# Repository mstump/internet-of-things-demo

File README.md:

internet-of-things-demo
=======================

Demo of internet of things

## Example Output:
```
motion: 0 | temp: 070.81°F | relative humidity: 045.75 | dew point: 048.85°F | pressure: 029.85 inHg | altitude: 039.20m
```

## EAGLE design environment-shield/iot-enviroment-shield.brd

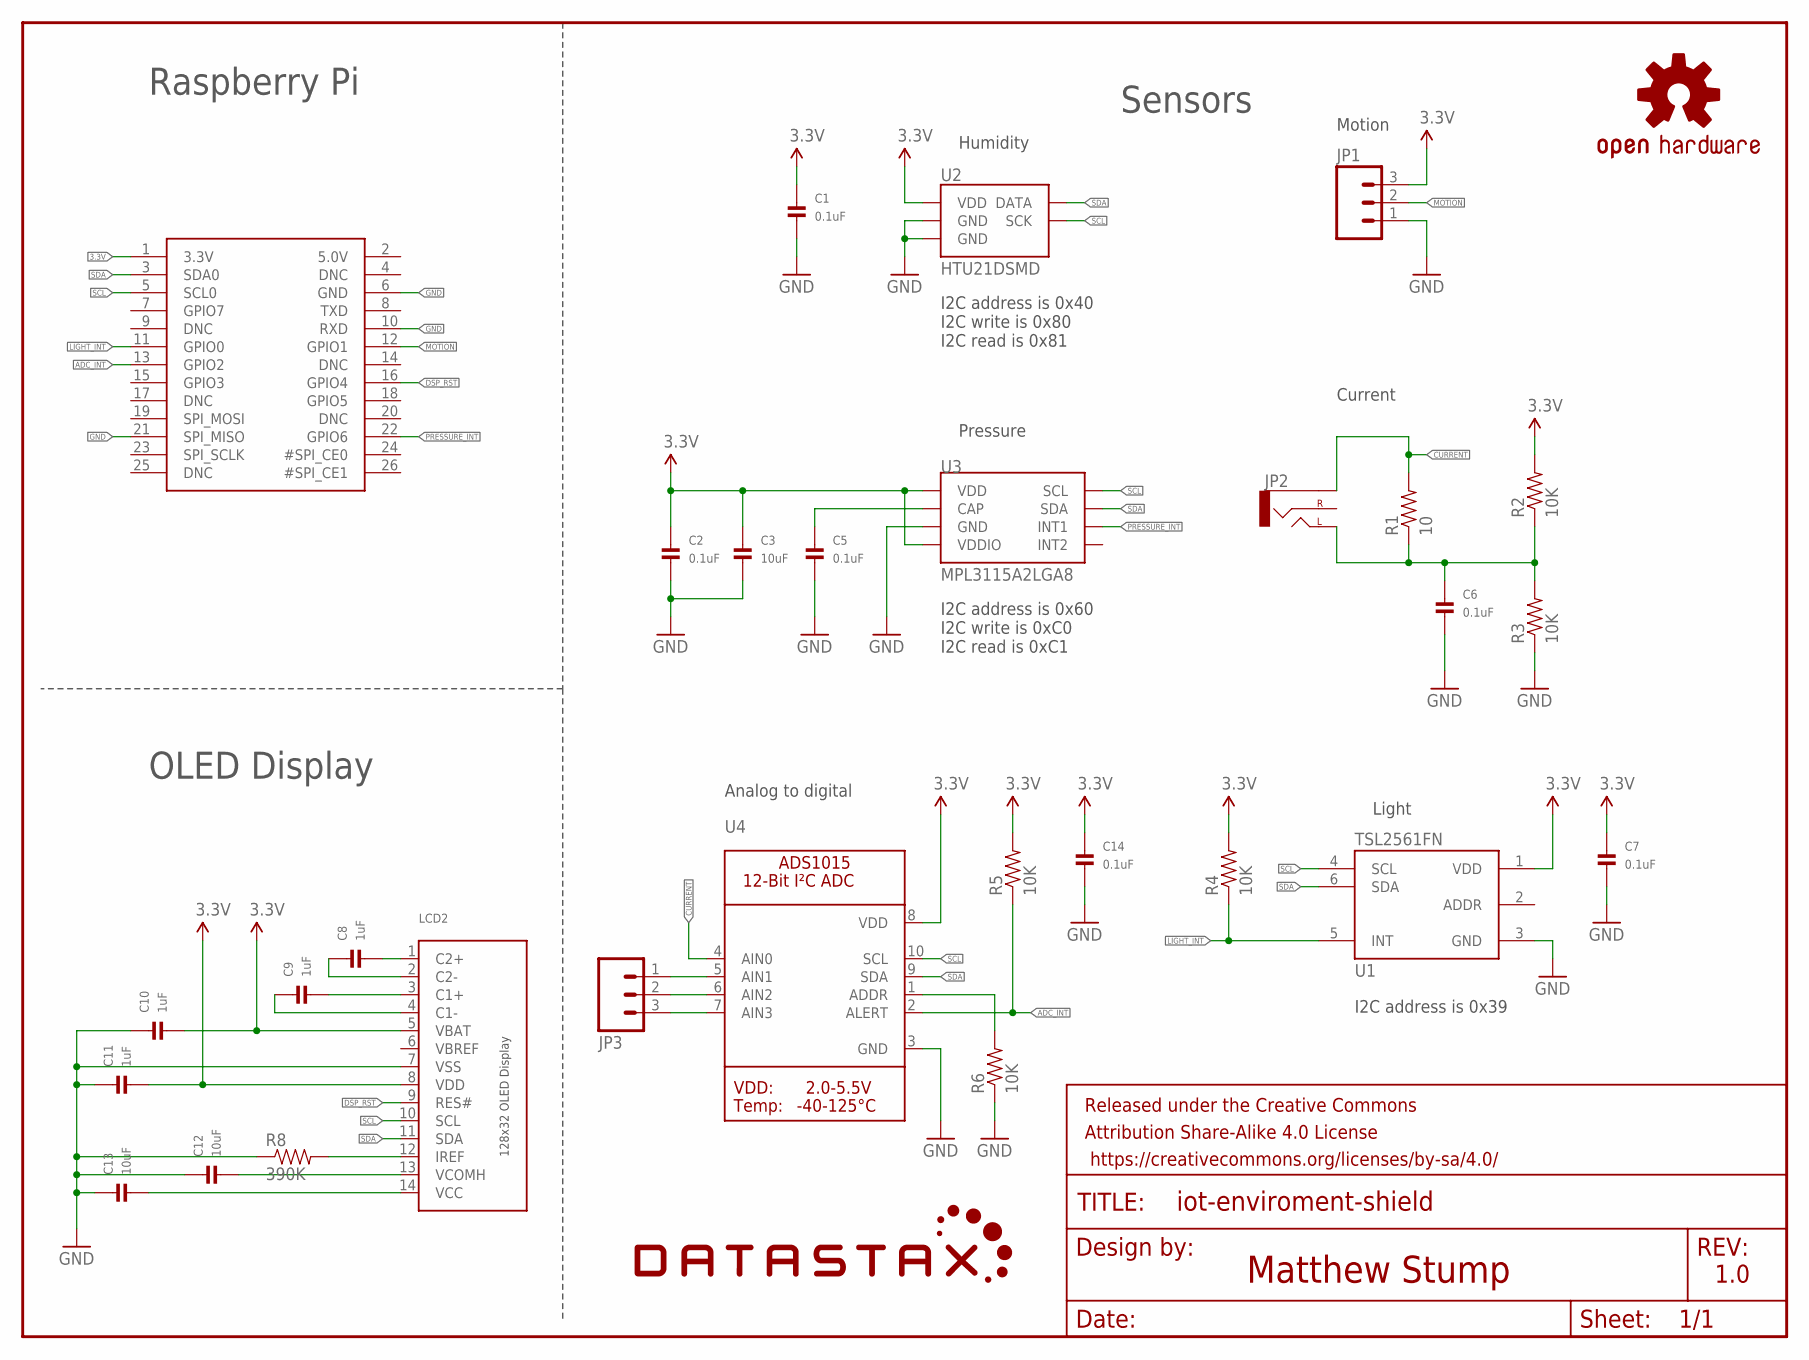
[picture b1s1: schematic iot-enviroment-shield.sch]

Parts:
C1, C2, C5, C6, C7, C14: 0.1uF; 0603; MPN 0603YC104JAT2A
C3, C12, C13: 10uF; 0603; MPN 06035A100FAT2A
C8, C9, C10, C11: 1uF; 0603; MPN 06036D105KAT2A
FRAME1: FRAME-LETTER; CREATIVE_COMMONS
JP1, JP3: M03SCREW; SCREWTERMINAL-3.5MM-3; MPN 1699680000
JP2: AUDIO-JACKPTH; AUDIO-JACK
LCD2: DISP_OLED_UG-2832HSWEG02; UG-2832HSWEG02_WRAPUNDER
LOGO1: OSHW-LOGOL; OSHW-LOGO-L
R1: 10; 0603-RES; MPN ERJ-3EKF10R0V
R2, R3, R4, R5, R6: 10K; 0603-RES; MPN ERJ-P03F1002V
R8: 390K; 0603-RES; MPN ERJ-P03F3903V
U1: TSL2561FN; FN-6; MPN TSL2561T
U2: HTU21DSMD; HTU21D; MPN HTU21D
U3: MPL3115A2LGA8; LGA8; MPN MPL3115A2
U4: ADC_ADS1015; MSOP10; MPN ADS1015IDGST
U$1: DATASTAX_LOGO
U$2: RASPBERRYPI_BB; RASBERRYPI_SHIELD

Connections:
3.3V: C1.1, C2.1, C3.1, C7.1, C10.2, C11.2, C14.1, JP1.3, LCD2.5 (VBAT), LCD2.8 (VDD), R2.2, R4.2, R5.2, U1.1 (VDD), U2.VDD, U3.1 (VDD), U3.4 (VDDIO), U4.8 (VDD), U$2.1 (3.3V)
ADC_INT: R5.1, U4.2 (ALERT), U$2.13 (GPIO2)
CURRENT: JP2.SLEEVE, R1.2, U4.4 (AIN0)
DSP_RST: LCD2.9 (RES#), U$2.16 (GPIO4)
GND: C1.2, C2.2, C3.2, C5.2, C6.2, C7.2, C10.1, C11.1, C12.1, C13.1, C14.2, JP1.1, LCD2.7 (VSS), R3.1, R6.1, R8.1, U1.3 (GND), U2.7 (GND), U2.GND, U3.3 (GND), U4.3 (GND), U$2.6 (GND), U$2.10 (RXD), U$2.21 (SPI_MISO)
LIGHT_INT: R4.1, U1.5 (INT), U$2.11 (GPIO0)
MOTION: JP1.2, U$2.12 (GPIO1)
unnamed: C5.1, U3.2 (CAP)
unnamed: JP3.1, U4.5 (AIN1)
unnamed: C6.1, JP2.TIP (LEFT), R1.1, R2.1, R3.2
unnamed: R6.2, U4.1 (ADDR)
unnamed: JP3.2, U4.6 (AIN2)
unnamed: JP3.3, U4.7 (AIN3)
unnamed: C8.2, LCD2.1 (C2+)
unnamed: C9.2, LCD2.3 (C1+)
unnamed: C13.2, LCD2.14 (VCC)
unnamed: LCD2.12 (IREF), R8.2
unnamed: C8.1, LCD2.2 (C2-)
unnamed: C9.1, LCD2.4 (C1-)
unnamed: C12.2, LCD2.13 (VCOMH)
PRESSURE_INT: U3.6 (INT1), U$2.22 (GPIO6)
SCL: LCD2.10 (SCL), U1.4 (SCL), U2.SCK, U3.8 (SCL), U4.10 (SCL), U$2.5 (SCL0)
SDA: LCD2.11 (SDA), U1.6 (SDA), U2.DATA, U3.7 (SDA), U4.9 (SDA), U$2.3 (SDA0)
VBREF: LCD2.6 (VBREF)

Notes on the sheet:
Light
Humidity
Pressure
Sensors
I2C address is 0x40 I2C write is 0x80 I2C read is 0x81
I2C address is 0x60 I2C write is 0xC0 I2C read is 0xC1
I2C address is 0x39
Current
Motion
Analog to digital
Raspberry Pi
OLED Display
Matthew Stump
1.0

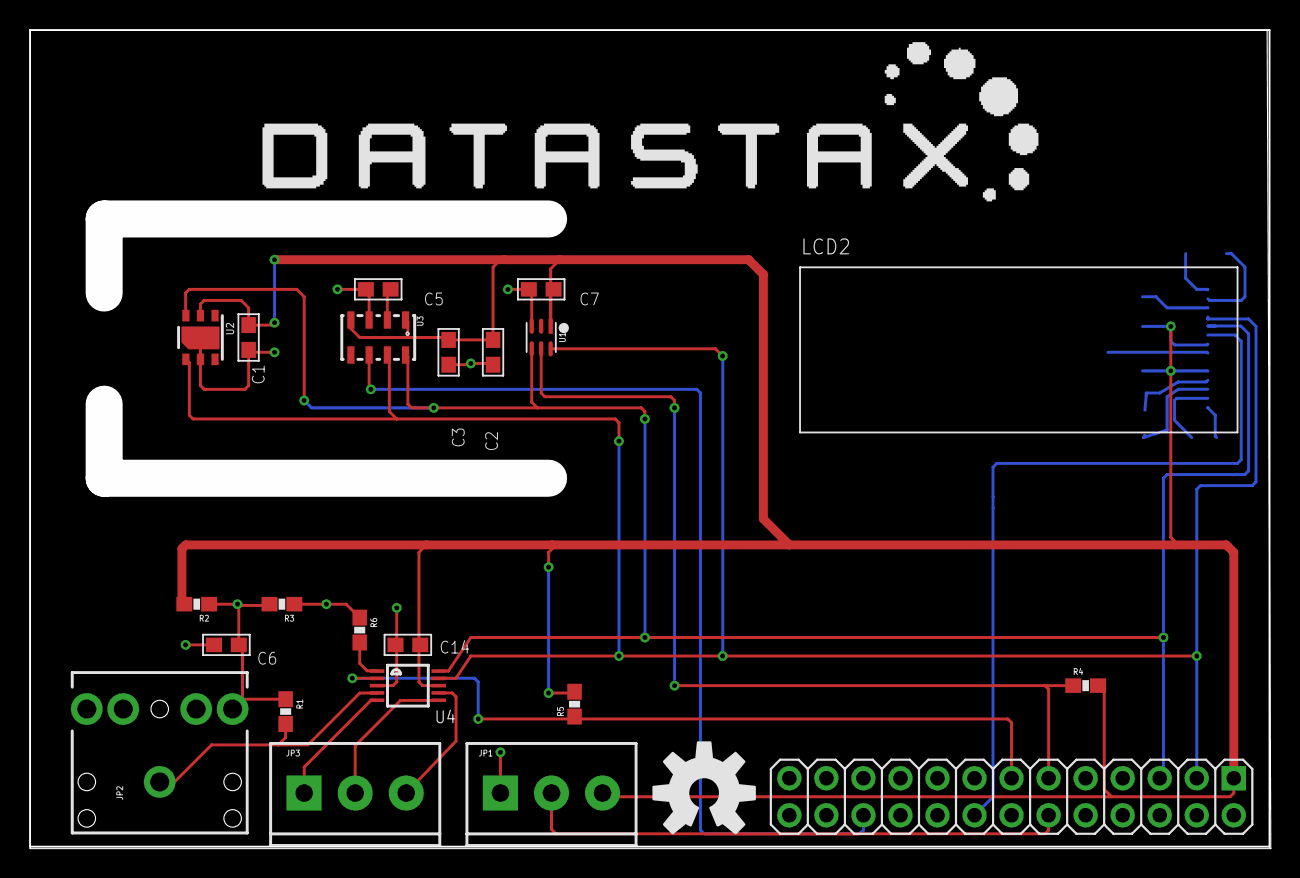
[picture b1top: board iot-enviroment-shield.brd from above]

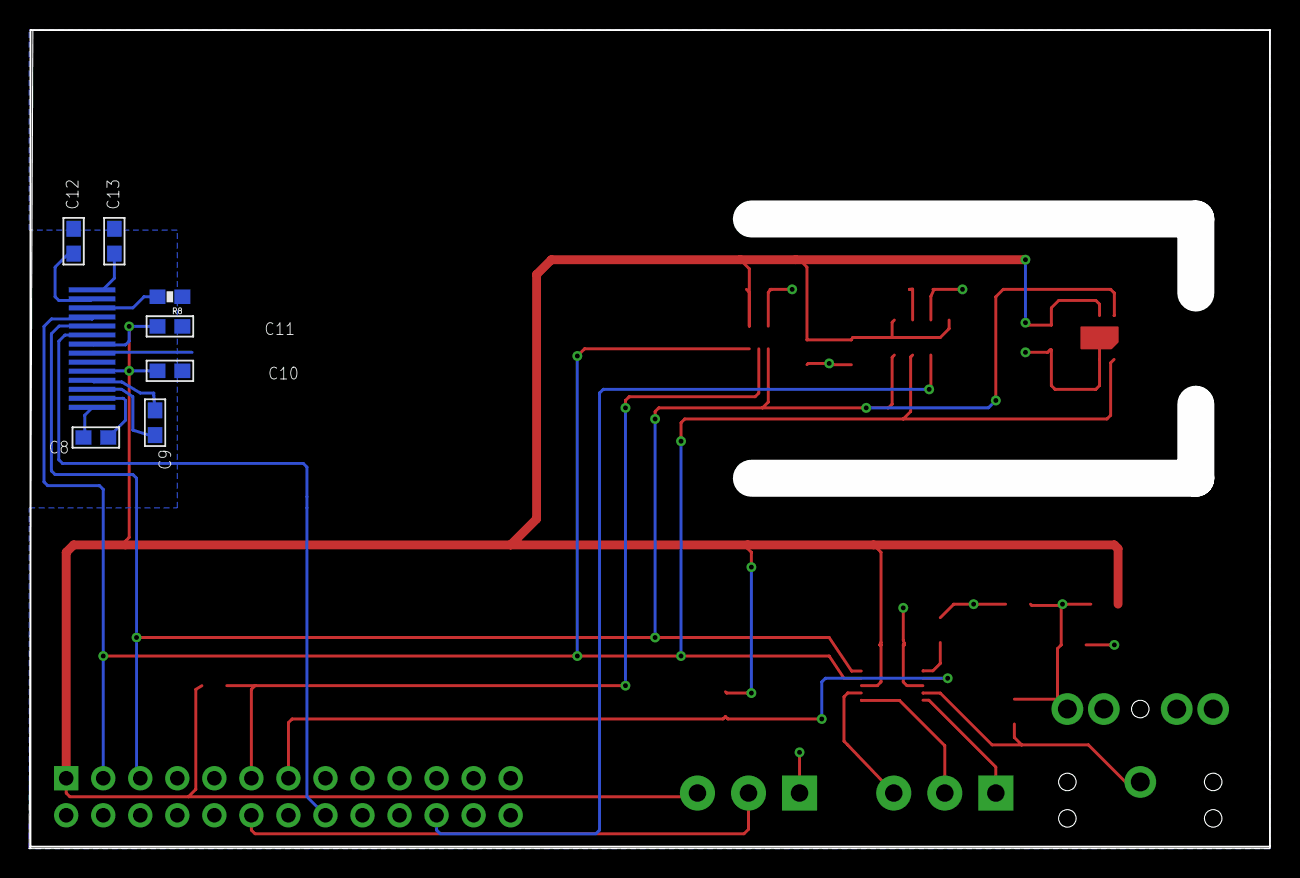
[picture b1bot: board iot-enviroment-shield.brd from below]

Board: 2 copper layers, 85.1 x 56.1 mm, 32 parts (7 on the bottom side), 23 nets.

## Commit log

2014-05-05 checkpoint
2014-05-05 cleanup
2014-05-06 checkpoint complete but untested temp/humidity sensor read code
2014-05-06 humidity, temp, and dew point are tested and working
2014-05-07 partial completion of barametric temp data
2014-05-07 pressure and altitude are complete and tested
2014-05-07 added example output to the README
2014-05-08 added script to read the camera and opencv cascades (detection data)
2014-06-06 adding board and schematic before switching to 0603 parts an I2C display
2014-06-08 switched to 603 components and an i2c display
2014-06-08 ground and power plane
2014-06-08 slot/cutout for thermal isolation
2014-06-09 removed the power plane, re-routed power, fixed all ERC and ERC errors
2014-06-25 rev1
2014-06-26 added python script to read tsl2561 light sensor
2014-07-02 add script to read a scale with the ADC

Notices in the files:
parts and their libraries:
SparkFun-Sensors: Licensing: Creative Commons ShareAlike 4.0 International - https://creativecommons.org/licenses/by-sa/4.0
SparkFun-Aesthetics: Released under the Creative Commons Attribution Share-Alike 4.0 License
SparkFun-Aesthetics: https://creativecommons.org/licenses/by-sa/4.0
